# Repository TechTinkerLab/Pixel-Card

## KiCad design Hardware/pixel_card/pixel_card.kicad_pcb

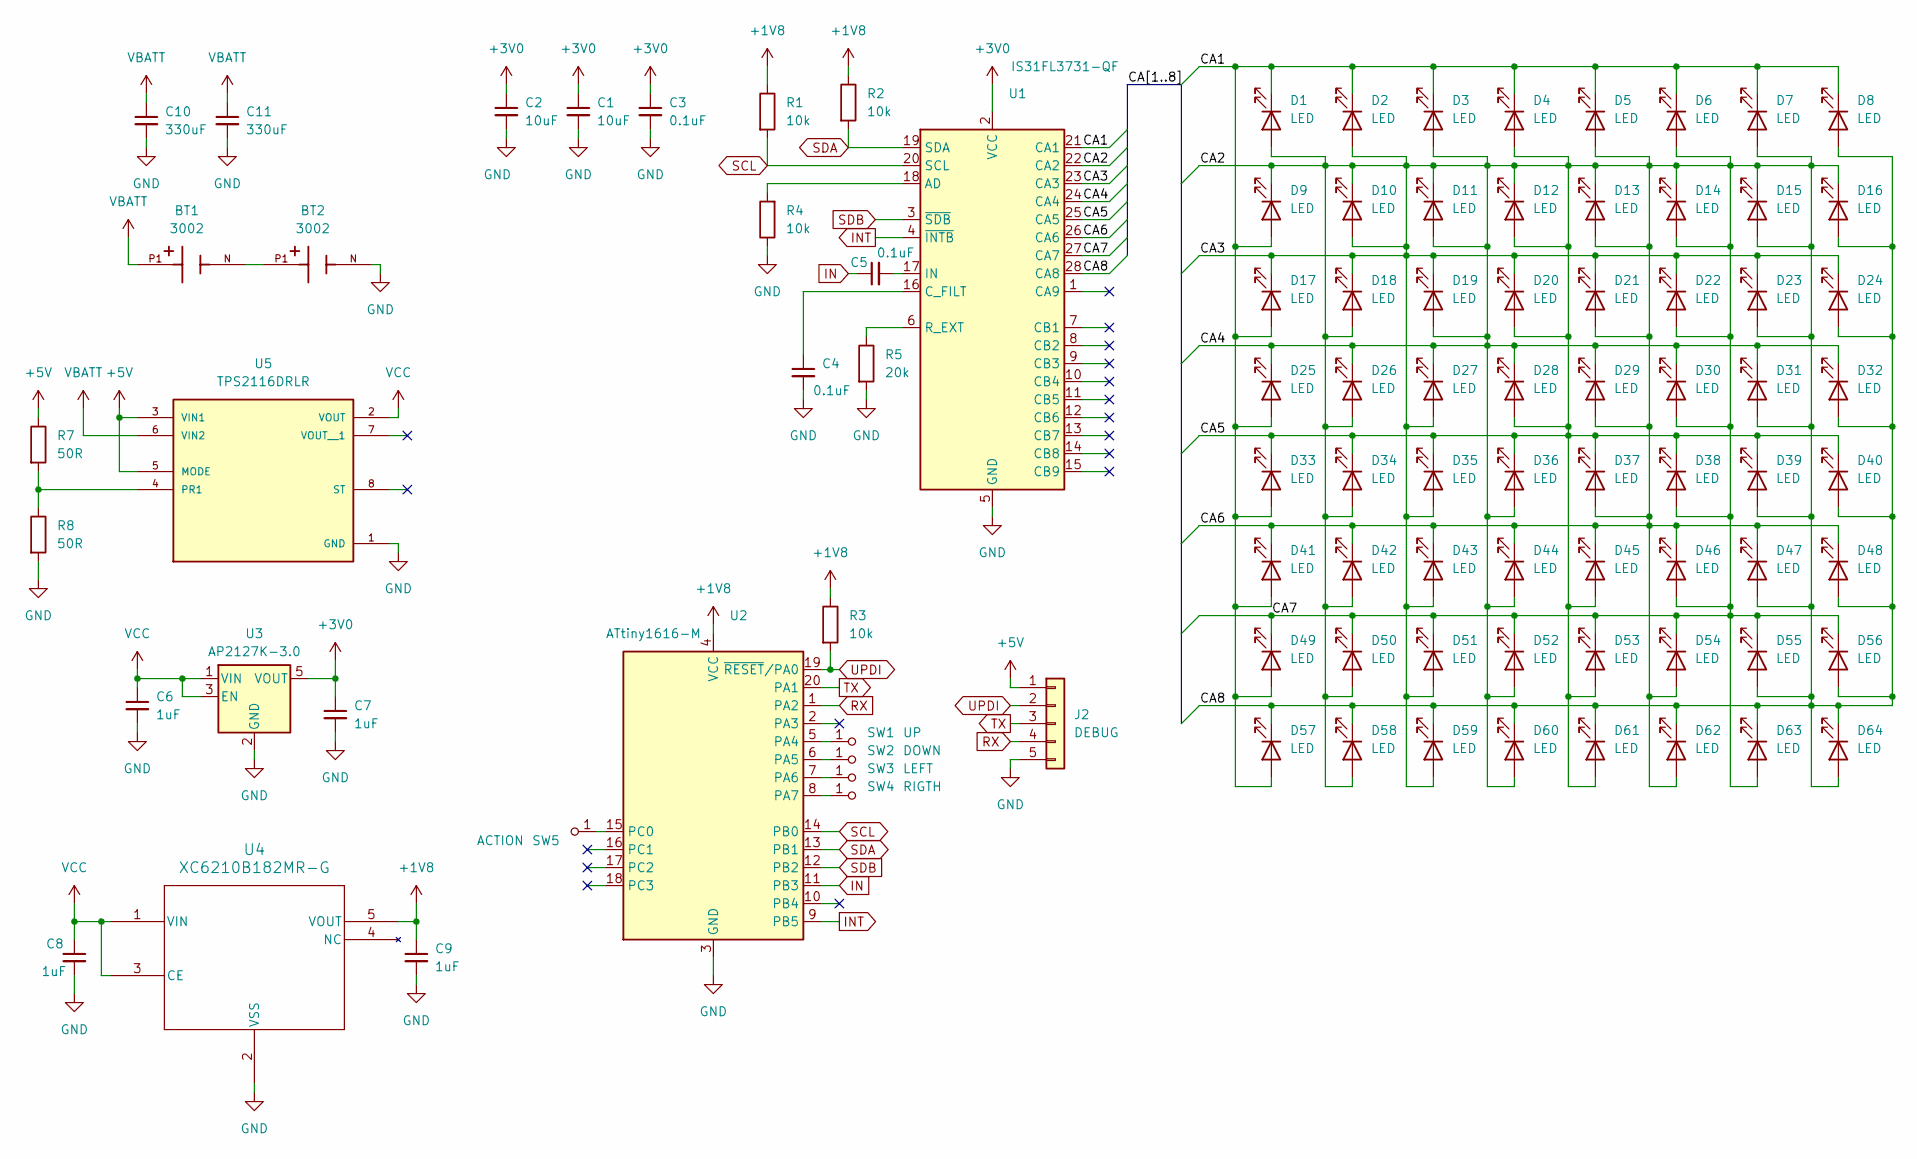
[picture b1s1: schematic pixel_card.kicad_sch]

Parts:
BT1, BT2: 3002; BAT_3002; PARTREV A
C1, C2: 10uF; C_0603_1608Metric
C3, C4, C5: 0.1uF; C_0603_1608Metric
C6, C7, C8, C9: 1uF; C_0603_1608Metric
C10, C11: 330uF; C_1206_3216Metric
D1, D2, D3, D4, D5, D6, D7, D8, D9, D10, D11, D12, D13, D14, D15, D16, D17, D18, D19, D20, D21, D22, D23, D24, D25, D26, D27, D28, D29, D30, D31, D32, D33, D34, D35, D36, D37, D38, D39, D40, D41, D42, D43, D44, D45, D46, D47, D48, D49, D50, D51, D52, D53, D54, D55, D56, D57, D58, D59, D60, D61, D62, D63, D64: LED; LED_0603_1608Metric
J2: DEBUG; 1X05
R1, R2, R3, R4: 10k; R_0603_1608Metric
R5: 20k; R_0603_1608Metric
R7, R8: 50R; R_0603_1608Metric
SW1: UP; Button-CapacitiveTouch
SW2: DOWN; Button-CapacitiveTouch
SW3: LEFT; Button-CapacitiveTouch
SW4: RIGTH; Button-CapacitiveTouch
SW5: ACTION; Button-CapacitiveTouch
U1: IS31FL3731-QF; QFN-28-1EP_4x4mm_P0.4mm_EP2.3x2.3mm
U2: ATtiny1616-M; VQFN-20-1EP_3x3mm_P0.4mm_EP1.7x1.7mm
U3: AP2127K-3.0; SOT-23-5
U4: XC6210B182MR-G; SOT-25_TOR
U5: TPS2116DRLR; SOTFL50P160X60-8N; PARTREV A

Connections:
+1V8: C9.1, R1.1, R2.1, R3.1, U2.4 (VCC), U4.5 (VOUT)
+3V0: C1.1, C2.1, C3.1, C7.1, U1.2 (VCC), U3.5 (VOUT)
+5V: J2.1, R7.1, U5.3 (VIN1), U5.5 (MODE)
/CA1: D1.1 (K), D2.1 (K), D3.1 (K), D4.1 (K), D5.1 (K), D6.1 (K), D7.1 (K), D8.1 (K), D9.2 (A), D17.2 (A), D25.2 (A), D33.2 (A), D41.2 (A), D49.2 (A), D57.2 (A), U1.21 (CA1)
/CA6: D1.2 (A), D2.2 (A), D3.2 (A), D4.2 (A), D5.2 (A), D6.2 (A), D7.2 (A), D8.2 (A), D9.1 (K), D10.1 (K), D10.2 (A), D11.1 (K), D11.2 (A), D12.1 (K), D12.2 (A), D13.1 (K), D13.2 (A), D14.1 (K), D14.2 (A), D15.1 (K), D15.2 (A), D16.1 (K), D16.2 (A), D17.1 (K), D18.1 (K), D18.2 (A), D19.1 (K), D19.2 (A), D20.1 (K), D20.2 (A), D21.1 (K), D21.2 (A), D22.1 (K), D22.2 (A), D23.1 (K), D23.2 (A), D24.1 (K), D24.2 (A), D25.1 (K), D26.1 (K), D26.2 (A), D27.1 (K), D27.2 (A), D28.1 (K), D28.2 (A), D29.1 (K), D29.2 (A), D30.1 (K), D30.2 (A), D31.1 (K), D31.2 (A), D32.1 (K), D32.2 (A), D33.1 (K), D34.1 (K), D34.2 (A), D35.1 (K), D35.2 (A), D36.1 (K), D36.2 (A), D37.1 (K), D37.2 (A), D38.1 (K), D38.2 (A), D39.1 (K), D39.2 (A), D40.1 (K), D40.2 (A), D41.1 (K), D42.1 (K), D42.2 (A), D43.1 (K), D43.2 (A), D44.1 (K), D44.2 (A), D45.1 (K), D45.2 (A), D46.1 (K), D46.2 (A), D47.1 (K), D47.2 (A), D48.1 (K), D48.2 (A), D49.1 (K), D50.1 (K), D50.2 (A), D51.1 (K), D51.2 (A), D52.1 (K), D52.2 (A), D53.1 (K), D53.2 (A), D54.1 (K), D54.2 (A), D55.1 (K), D55.2 (A), D56.1 (K), D56.2 (A), D57.1 (K), D58.1 (K), D58.2 (A), D59.1 (K), D59.2 (A), D60.1 (K), D60.2 (A), D61.1 (K), D61.2 (A), D62.1 (K), D62.2 (A), D63.1 (K), D63.2 (A), D64.1 (K), D64.2 (A), U1.22 (CA2), U1.23 (CA3), U1.24 (CA4), U1.25 (CA5), U1.26 (CA6), U1.27 (CA7), U1.28 (CA8)
GND: BT2.N, C1.2, C2.2, C3.2, C4.2, C6.2, C7.2, C8.2, C9.2, C10.2, C11.2, J2.5, R4.1, R5.2, R8.2, U1.5 (GND), U1.29 (GND), U2.3 (GND), U2.21 (GND), U3.2 (GND), U4.2 (VSS), U5.1 (GND)
IN: C5.1, U2.11 (PB3)
INT: U1.4 (~INTB), U2.9 (PB5)
unnamed: BT1.N, BT2.P1
unnamed: SW1.1 (A), U2.5 (PA4)
unnamed: SW2.1 (A), U2.6 (PA5)
unnamed: SW3.1 (A), U2.7 (PA6)
unnamed: SW4.1 (A), U2.8 (PA7)
unnamed: SW5.1 (A), U2.15 (PC0)
unnamed: R4.2, U1.18 (AD)
unnamed: C4.1, U1.16 (C_FILT)
unnamed: C5.2, U1.17 (IN)
unnamed: R5.1, U1.6 (R_EXT)
unnamed: R7.2, R8.1, U5.4 (PR1)
RX: J2.4, U2.1 (PA2)
SCL: R1.2, U1.20 (SCL), U2.14 (PB0)
SDA: R2.2, U1.19 (SDA), U2.13 (PB1)
SDB: U1.3 (~SDB), U2.12 (PB2)
TX: J2.3, U2.20 (PA1)
UPDI: J2.2, R3.2, U2.19 (~RESET/PA0)
VBATT: BT1.P1, C10.1, C11.1, U5.6 (VIN2)
VCC: C6.1, C8.1, U3.1 (VIN), U3.3 (EN), U4.1 (VIN), U4.3 (CE), U5.2 (VOUT)

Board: 2 copper layers, 95 parts (0 on the bottom side), 27 nets, no tracks yet.

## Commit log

2024-05-21 Init commit and adding current hadware schematic
2024-05-21 Organizing folder structure and adding additional kicad libs
2024-05-22 Creating pcb outline
2024-05-22 Adding kicad lib for Keystone 3002
2024-05-22 Coin cell battery design, end routing power mux
    1. Designing circuit for double CR2032 batteries with additional
    capacitors to help during huge current
    2. Added voltage divider for power mux (2x 50Ohm should always give
    voltage above 1V Vref of power mux)
    3. Started cleaning schematic
2024-05-23 Finishing schematic
    1. Cleaning up schematic
    2. Running and fixing erros from electrical rule check
2024-05-23 Fixing schematic and mocing to pcb
    1. Adding not-connected pin symbols
    2. Adding footprints
